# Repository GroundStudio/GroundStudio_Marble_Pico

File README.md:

GroundStudio Marble Pico
====================================

Get it from:

[digikey.com](https://www.digikey.com/en/products/detail/groundstudio/RLJDMV-AAA/21080805)

[ardushop.ro](https://ardushop.ro/en/groundstudio/1590-marble-pico-6427854000682.html)

Explore all the GroundStudio products at [ardushop.ro](https://ardushop.ro/en/37-groundstudio)

Description
-------------------
RP2040 based development board with 26 GPIO, 16 controllable PWM channels, three 12-bit ADC with dedicated ADC voltage reference, 8MB external SPI Flash memory, I²C 3V3 adapter and microSD card adapter.

Contents
-------------------

* [/Documentation](https://github.com/GroundStudio/GroundStudio_Marble_Pico/tree/main/Documentation) -- Contains documentation written during creation of this repository, with readme.md index of its own!
* [/Firmware](https://github.com/GroundStudio/GroundStudio_Marble_Pico/tree/main/Firmware) -- Firmware (bootloaders, etc)
* [/Hardware](https://github.com/GroundStudio/GroundStudio_Marble_Pico/tree/main/Hardware) -- Schematics, layout.
* [/Libraries](https://github.com/GroundStudio/GroundStudio_Marble_Pico/tree/main/Libraries) -- Arduino/CircuitPython libraries. 

Versions
-------------------
*(Not all tags shown)*
* [V0.0.3] Initial release version

License
-------------------
This is released under the [Attribution-ShareAlike 4.0 International (CC BY-SA 4.0)](https://creativecommons.org/licenses/by-sa/4.0/) license. 
**You are welcome to use this for commercial purposes.**

Please consider contributing back to this project or others to help the open-source hardware community continue to thrive and grow! 

Certifications:   
[Open Source Hardware Association](https://certification.oshwa.org/ro000001.html)

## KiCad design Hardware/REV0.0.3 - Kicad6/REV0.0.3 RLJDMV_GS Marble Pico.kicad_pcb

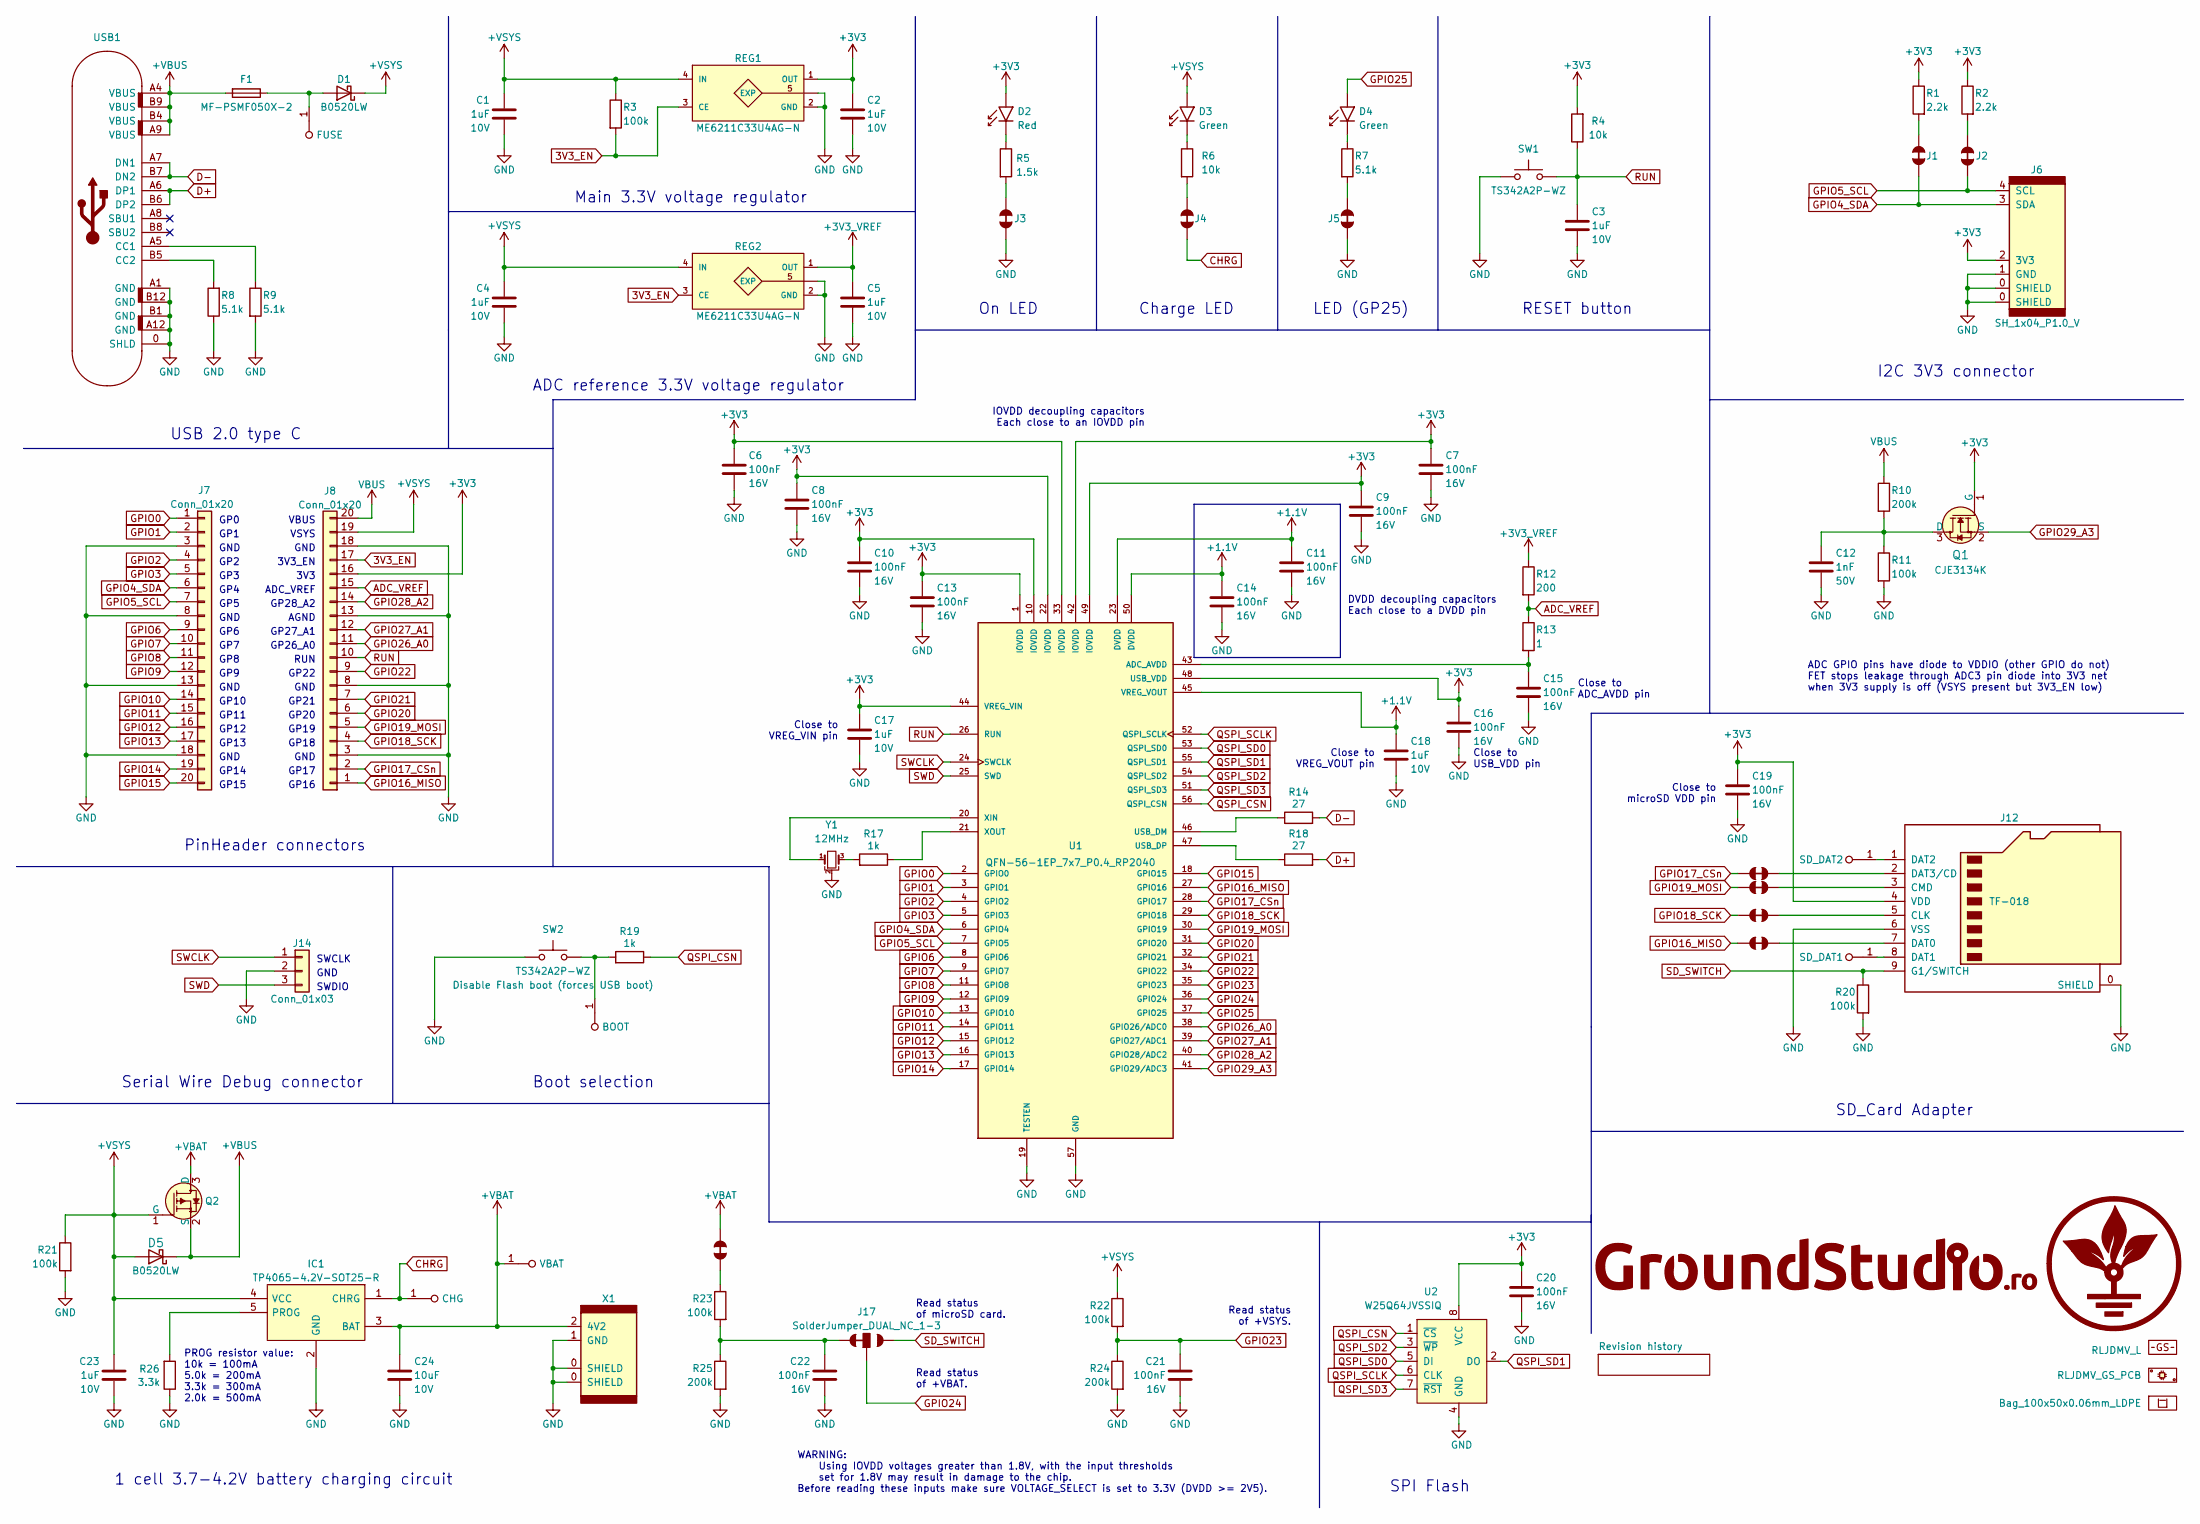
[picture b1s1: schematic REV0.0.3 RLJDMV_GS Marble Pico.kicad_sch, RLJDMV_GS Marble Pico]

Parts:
B1: Bag_100x50x0.06mm_LDPE; MPN KFHHEG_B
C1, C2, C3, C4, C5, C17, C18, C23: C_0402_1uF_10V; C_0402_alt; Rated voltage 10V; MPN FS15B105K100PKG; LCSC C525324
C6, C7, C8, C9, C10, C11, C13, C14, C15, C16, C19, C20, C21, C22: C_0402_100nF_16V; C_0402_alt; Rated voltage 16V; MPN 0402B104K160CT; LCSC C83056
C12: C_0402_1nF_50V; C_0402_alt; Rated voltage 50V; MPN CC0402KRX7R9BB102; LCSC C106205
C24: C_0402_10uF_10V; C_0402_alt; Rated voltage 10V; MPN LDK105CBJ106MVLF; LCSC C386033
D1, D5: SOD-123_B0520LW; SOD-123; MPN B0520LW; LCSC C89640
D2: LED_0402_RED; LED_0402_alt; MPN TZ-P2-0402RTIA1-0.45T; LCSC C779449
D3, D4: LED_0402_GREEN; LED_0402_alt; MPN TZ-P2-0402GTIA1-0.45T; LCSC C688877
F1: Fuse_0805_MF-PSMF050X-2; Fuse_0805; MPN MF-PSMF050X-2; LCSC C116170
IC1: SOT23-5_TP4065-4.2V; SOT-23-5; MPN TP4065-4.2V-SOT25-R; LCSC C113540
J1, J2, J3, J4, J5, J10, J11, J13, J15: SolderJumper_NC
J6: SH_1x04_P1.0_V; SH__1x04_P1.00mm_Vertical; MPN C145961; LCSC C145961
J7, J8: Conn_01x20; PinHeader_1x20_P2.54mm_Vertical_Male; MPN B-2100S20P-A110; LCSC C124374
J12: TF-018_microSD; TF-018; MPN TF-018; LCSC C961679
J14: Conn_01x03; PinHeader_1x03_P2.54mm_Vertical_Male; MPN C49257; LCSC C49257
J17: SolderJumper_DUAL_NC_1-3
J100: SolderJumper_NC; SolderJumper_NC_Default
L1: RLJDMV_L; MPN RLJDMV_L
P1: PCB; MPN RLJDMV_GS_PCB
Q1: SOT-523_CJE3134K; SOT-523; MPN CJE3134K; LCSC C504104
Q2: SOT-883 LP0404N3T5G; SOT-883; MPN LP0404N3T5G; LCSC C172433
R1, R2: R_0402_2.2k; R_0402_alt; MPN RC-02W2201FT; LCSC C258093
R3, R11, R20, R21, R22, R23: R_0402_100k; R_0402_alt; MPN 0402WGF1003TCE; LCSC C25741
R4, R6: R_0402_10k; R_0402_alt; MPN 0402WGJ0103TCE; LCSC C25531
R5: R_0402_1.5k; R_0402_alt; MPN 0402WGF1501TCE; LCSC C25867
R7, R8, R9: R_0402_5.1k; R_0402_alt; MPN RC-02W5101FT; LCSC C294638
R10, R24, R25: R_0402_200k; R_0402_alt; MPN 0402WGF2003TCE; LCSC C25764
R12: R_0402_200; R_0402_alt; MPN HPCR0402F200RK9; LCSC C364967
R13: R_0402_1; R_0402_alt; MPN RC-02U1R00FT; LCSC C140193
R14, R18: R_0402_27; R_0402_alt; MPN 0402WGF270JTCE; LCSC C25100
R17, R19: R_0402_1k; R_0402_alt; MPN RC-02W1001FT; LCSC C226166
R26: R_0402_3.3k; R_0402_alt; MPN RC-02W3301FT; LCSC C310224
REG1, REG2: FBP1-1-4_ME6211C33U4AG-N; FBP1-1-4; MPN ME6211C33U4AG-N; LCSC C428904
SW1, SW2: TS342A2P-WZ; MPN TS342A2P-WZ; LCSC C557591
TP1: FUSE; TestPoint
TP2: BOOT; TestPoint
TP3: CHG; TestPoint
TP4: VBAT; TestPoint
TP100: SD_DAT2; TestPoint
TP101: SD_DAT1; TestPoint
U1: QFN-56-1EP_7x7_P0.4_RP2040; QFN-56-1EP_7x7mm_P0.4mm_EP4x4mm; MPN RP2040; LCSC C2040
U2: SOIC-8_5.275x5.275_W25Q64JV; SOIC-8_5.275x5.275mm_P1.27mm; MPN W25Q64JVSSIQ; LCSC C83140
USB1: USB_C_FULL; USB_C_C167321; MPN 918-418K2023S40001; LCSC C167321
X1: PH__1x02_P2.0_H; PH__1x02_P2.00mm_Horizontal; MPN C47647; LCSC C47647
Y1: RSN_3P_3.2x1.3_CSTNE12; Rsn_muRata_CSTxE-3Pin_3.2x1.3mm; MPN CSTNE12M0G550000R0; LCSC C341520

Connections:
3V3_EN: J8.17, R3.2, REG1.3 (CE), REG2.3 (CE)
+1.1V: C11.1, C14.1, C18.1, U1.23 (DVDD), U1.45 (VREG_VOUT), U1.50 (DVDD)
+3V3: C2.1, C6.1, C7.1, C8.1, C9.1, C10.1, C13.1, C16.1, C17.1, C19.1, C20.1, D2.2 (A), J6.2 (3V3), J8.16, J12.4 (VDD), Q1.1 (G), R1.1, R2.1, R4.2, REG1.1 (OUT), U1.1 (IOVDD), U1.10 (IOVDD), U1.22 (IOVDD), U1.33 (IOVDD), U1.42 (IOVDD), U1.44 (VREG_VIN), U1.48 (USB_VDD), U1.49 (IOVDD), U2.8 (VCC)
+3V3_VREF: C5.1, R12.1, REG2.1 (OUT)
+VBAT: C24.1, IC1.3 (BAT), J100.2, Q2.3 (D), TP4.1, X1.2 (4V2)
+VSYS: C1.2, C4.2, C23.1, D1.1 (K), D3.2 (A), D5.2 (A), IC1.4 (VCC), J8.19, Q2.1 (G), R3.1, R21.1, R22.1, REG1.4 (IN), REG2.4 (IN)
ADC_VREF: J8.15, R12.2, R13.1
CHRG: IC1.1 (CHRG), J4.1, TP3.1
D+: R18.2, USB1.A6 (DP1), USB1.B6 (DP2)
D-: R14.2, USB1.A7 (DN1), USB1.B7 (DN2)
GND: C1.1, C2.2, C3.2, C4.1, C5.2, C6.2, C7.2, C8.2, C9.2, C10.2, C11.2, C12.2, C13.2, C14.2, C15.2, C16.2, C17.2, C18.2, C19.2, C20.2, C21.2, C22.2, C23.2, C24.2, IC1.2 (GND), J3.1, J5.1, J6.0 (SHIELD), J6.1 (GND), J7.3, J7.8, J7.13, J7.18, J8.3, J8.8, J8.13, J8.18, J12.0 (SHIELD), J12.6 (VSS), J14.2, R8.1, R9.2, R11.2, R20.2, R21.2, R24.2, R25.2, R26.1, REG1.2 (GND), REG1.5 (EXP), REG2.2 (GND), REG2.5 (EXP), SW1.1, SW2.1, U1.19 (TESTEN), U1.57 (GND), U2.4 (GND), USB1.0 (SHLD), USB1.A1 (GND), USB1.A12 (GND), USB1.B1 (GND), USB1.B12 (GND), X1.0 (SHIELD), X1.1 (GND), Y1.2
GPIO0: J7.1, U1.2 (GPIO0)
GPIO1: J7.2, U1.3 (GPIO1)
GPIO2: J7.4, U1.4 (GPIO2)
GPIO3: J7.5, U1.5 (GPIO3)
GPIO4_SDA: J1.2, J6.3 (SDA), J7.6, U1.6 (GPIO4)
GPIO5_SCL: J2.1, J6.4 (SCL), J7.7, U1.7 (GPIO5)
GPIO6: J7.9, U1.8 (GPIO6)
GPIO7: J7.10, U1.9 (GPIO7)
GPIO8: J7.11, U1.11 (GPIO8)
GPIO9: J7.12, U1.12 (GPIO9)
GPIO10: J7.14, U1.13 (GPIO10)
GPIO11: J7.15, U1.14 (GPIO11)
GPIO12: J7.16, U1.15 (GPIO12)
GPIO13: J7.17, U1.16 (GPIO13)
GPIO14: J7.19, U1.17 (GPIO14)
GPIO15: J7.20, U1.18 (GPIO15)
GPIO16_MISO: J8.1, J15.2, U1.27 (GPIO16)
GPIO17_CSn: J8.2, J10.2, U1.28 (GPIO17)
GPIO18_SCK: J8.4, J13.2, U1.29 (GPIO18)
GPIO19_MOSI: J8.5, J11.2, U1.30 (GPIO19)
GPIO20: J8.6, U1.31 (GPIO20)
GPIO21: J8.7, U1.32 (GPIO21)
GPIO22: J8.9, U1.34 (GPIO22)
GPIO23: C21.1, R22.2, R24.1, U1.35 (GPIO23)
GPIO24: J17.3, U1.36 (GPIO24)
GPIO25: D4.2 (A), U1.37 (GPIO25)
GPIO26_A0: J8.11, U1.38 (GPIO26/ADC0)
GPIO27_A1: J8.12, U1.39 (GPIO27/ADC1)
GPIO28_A2: J8.14, U1.40 (GPIO28/ADC2)
GPIO29_A3: Q1.2 (S), U1.41 (GPIO29/ADC3)
unnamed: C12.1, Q1.3 (D), R10.2, R11.1
unnamed: C15.1, R13.2, U1.43 (ADC_AVDD)
unnamed: C22.1, J17.1, R23.2, R25.1
unnamed: D1.2 (A), F1.1, TP1.1
unnamed: D2.1 (K), R5.1
unnamed: D3.1 (K), R6.1
unnamed: D4.1 (K), R7.1
unnamed: IC1.5 (PROG), R26.2
unnamed: J1.1, R1.2
unnamed: J2.2, R2.2
unnamed: J3.2, R5.2
unnamed: J4.2, R6.2
unnamed: J5.2, R7.2
unnamed: J10.1, J12.2 (DAT3/CD)
unnamed: J11.1, J12.3 (CMD)
unnamed: J12.1 (DAT2), TP100.1
unnamed: J12.5 (CLK), J13.1
unnamed: J12.7 (DAT0), J15.1
unnamed: J12.8 (DAT1), TP101.1
unnamed: J100.1, R23.1
unnamed: R8.2, USB1.B5 (CC2)
unnamed: R9.1, USB1.A5 (CC1)
unnamed: R14.1, U1.46 (USB_DM)
unnamed: R17.1, U1.21 (XOUT)
unnamed: R17.2, Y1.3
unnamed: R18.1, U1.47 (USB_DP)
unnamed: R19.2, SW2.2, TP2.1
unnamed: U1.20 (XIN), Y1.1
QSPI_CSN: R19.1, U1.56 (QSPI_CSN), U2.1 (~CS)
QSPI_SCLK: U1.52 (QSPI_SCLK), U2.6 (CLK)
QSPI_SD0: U1.53 (QSPI_SD0), U2.5 (DI)
QSPI_SD1: U1.55 (QSPI_SD1), U2.2 (DO)
QSPI_SD2: U1.54 (QSPI_SD2), U2.3 (~WP)
QSPI_SD3: U1.51 (QSPI_SD3), U2.7 (~RST)
RUN: C3.1, J8.10, R4.1, SW1.2, U1.26 (RUN)
SD_SWITCH: J12.9 (G1/SWITCH), J17.2, R20.1
SWCLK: J14.1, U1.24 (SWCLK)
SWD: J14.3, U1.25 (SWD)

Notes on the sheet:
Main 3.3V voltage regulator
GND
USB 2.0 type C
Boot selection
GP17
GP20
GP2
GP18
RESET button
Read status of microSD card.
GP15
VSYS
GP11
GP10
GP8
Charge LED
GP3
GP9
GP22
Close to USB_VDD pin
Serial Wire Debug connector
SWDIO
SWCLK
RUN
GP7
Close to microSD VDD pin
GP19
SPI Flash
Close to VREG_VOUT pin
GP12
ADC GPIO pins have diode to VDDIO (other GPIO do not) FET stops leakage through ADC3 pin diode into 3V3 net when 3V3 supply is off (VSYS present but 3V3_EN low)
ADC reference 3.3V voltage regulator
GP26_A0
GP14
IOVDD decoupling capacitors Each close to an IOVDD pin
ADC_VREF
GP5
LED (GP25)
On LED
GP0

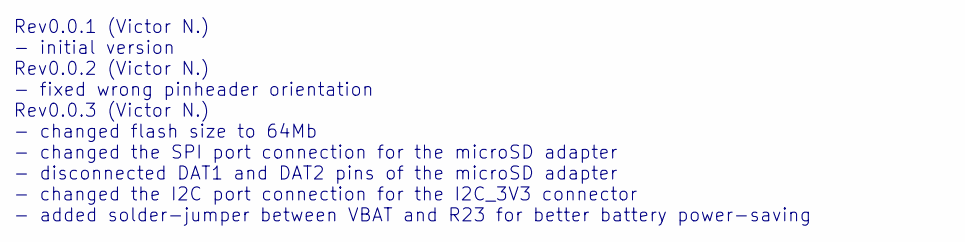
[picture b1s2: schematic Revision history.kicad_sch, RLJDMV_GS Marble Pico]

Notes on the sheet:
Rev0.0.1 (Victor N.) - initial version Rev0.0.2 (Victor N.) - fixed wrong pinheader orientation Rev0.0.3 (Victor N.) - changed flash size to 64Mb - changed the SPI port connection for the microSD adapter - disconnected DAT1 and DAT2 pins of the microSD adapter - changed the I2C port connection for 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

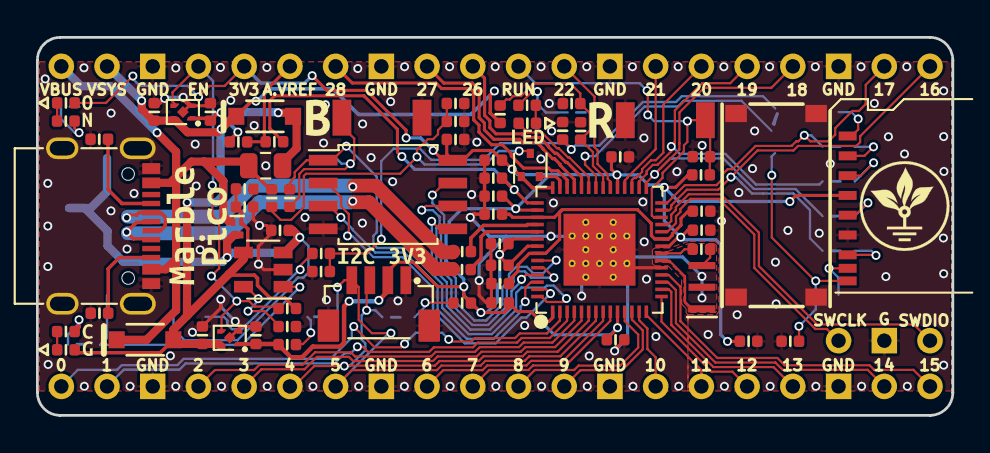
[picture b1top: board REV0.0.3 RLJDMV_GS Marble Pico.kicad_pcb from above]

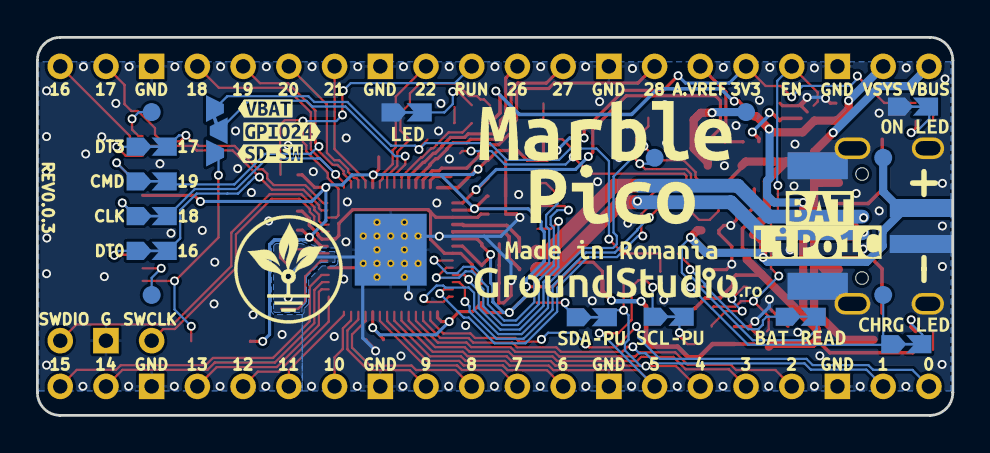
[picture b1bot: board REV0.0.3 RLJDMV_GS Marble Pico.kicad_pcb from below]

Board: 2 copper layers, 50.9 x 21.0 mm, 112 parts (29 on the bottom side), 80 nets.

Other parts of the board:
kibuzzard-632C0BB6: G***; kibuzzard-632C0BB6
kibuzzard-632C0BC8: G***; kibuzzard-632C0BC8
kibuzzard-639AEA0F: G***; kibuzzard-639AEA0F
kibuzzard-639B16C2: G***; kibuzzard-639B16C2
kibuzzard-63497F21: G***; kibuzzard-63497F21
kibuzzard-634012B7: G***; kibuzzard-634012B7
kibuzzard-634012BF: G***; kibuzzard-634012BF
kibuzzard-634014D4: G***; kibuzzard-634014D4
kibuzzard-634022BB: G***; kibuzzard-634022BB
kibuzzard-634022DD: G***; kibuzzard-634022DD
kibuzzard-6340151A: G***; kibuzzard-6340151A
kibuzzard-6340179C: G***; kibuzzard-6340179C
kibuzzard-6340242C: G***; kibuzzard-6340242C
kibuzzard-6340244C: G***; kibuzzard-6340244C
kibuzzard-6340246F: G***; kibuzzard-6340246F
kibuzzard-6340261C: G***; kibuzzard-6340261C
kibuzzard-63401192: G***; kibuzzard-63401192
kibuzzard-63401212: G***; kibuzzard-63401212
kibuzzard-63401226: G***; kibuzzard-63401226
kibuzzard-63401276: G***; kibuzzard-63401276
kibuzzard-63401294: G***; kibuzzard-63401294
kibuzzard-63402330: G***; kibuzzard-63402330
kibuzzard-63402571: G***; kibuzzard-63402571
kibuzzard-63402583: G***; kibuzzard-63402583

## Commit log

2023-03-15 Update README.md
    - removed references to "library"
2023-11-03 - added datasheet
2023-12-07 - updated pinout and datasheet to REV 1.1
2024-04-07 Update README.md
    - added digikey link
2025-02-18 - added 3D step file
2025-09-10 Update ardushop.ro shop links
